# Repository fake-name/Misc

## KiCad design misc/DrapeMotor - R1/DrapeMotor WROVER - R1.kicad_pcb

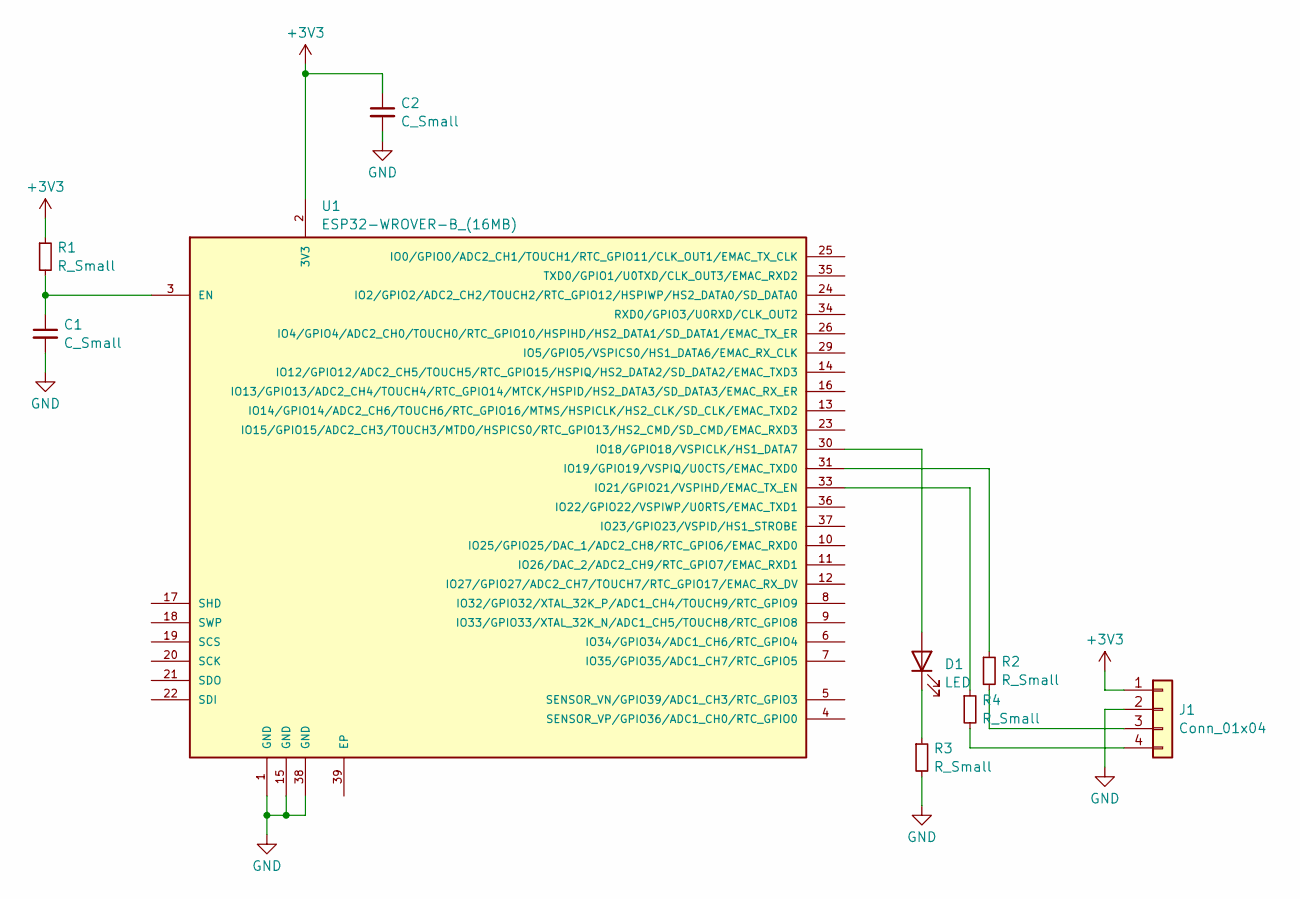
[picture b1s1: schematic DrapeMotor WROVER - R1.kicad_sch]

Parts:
C1, C2: C_Small; C_1206_3216Metric_Pad1.33x1.80mm_HandSolder
D1: LED; D_1206_3216Metric_Pad1.42x1.75mm_HandSolder
J1: Conn_01x04; PinSocket_1x04_P2.54mm_Vertical
R1, R2, R3, R4: R_Small; R_1206_3216Metric_Pad1.30x1.75mm_HandSolder
U1: ESP32-WROVER-B_(16MB); XCVR_ESP32-WROVER-B_(16MB); PARTREV 1.1

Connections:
+3V3: C2.1, J1.1, R1.1, U1.2 (3V3)
GND: C1.2, C2.2, J1.2, R3.2, U1.1 (GND), U1.15 (GND), U1.38 (GND)
unnamed: D1.2 (A), U1.30 (IO18/GPIO18/VSPICLK/HS1_DATA7)
unnamed: D1.1 (K), R3.1
unnamed: J1.3, R2.2
unnamed: J1.4, R4.2
unnamed: C1.1, R1.2, U1.3 (EN)
unnamed: R2.1, U1.31 (IO19/GPIO19/VSPIQ/U0CTS/EMAC_TXD0)
unnamed: R4.1, U1.33 (IO21/GPIO21/VSPIHD/EMAC_TX_EN)

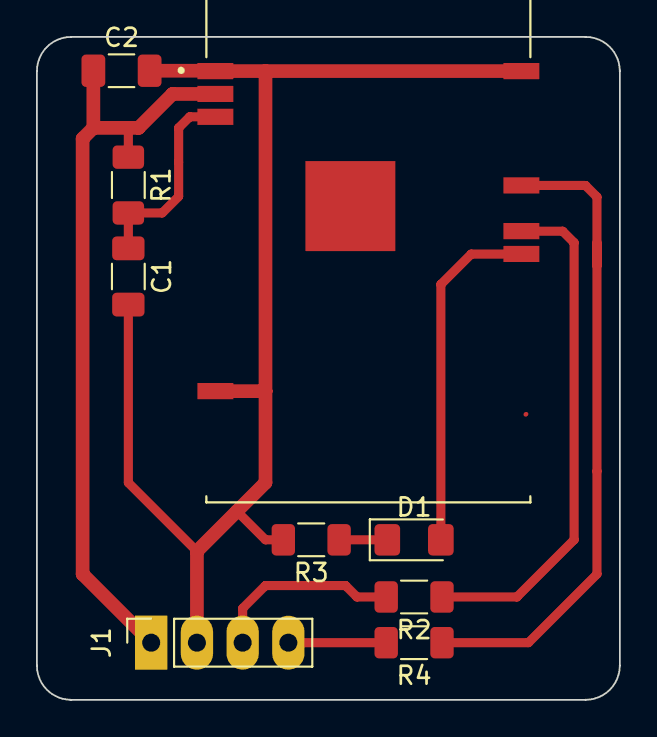
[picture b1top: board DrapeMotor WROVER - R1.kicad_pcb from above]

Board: 2 copper layers, 32.4 x 36.8 mm, 9 parts (0 on the bottom side), 9 nets.

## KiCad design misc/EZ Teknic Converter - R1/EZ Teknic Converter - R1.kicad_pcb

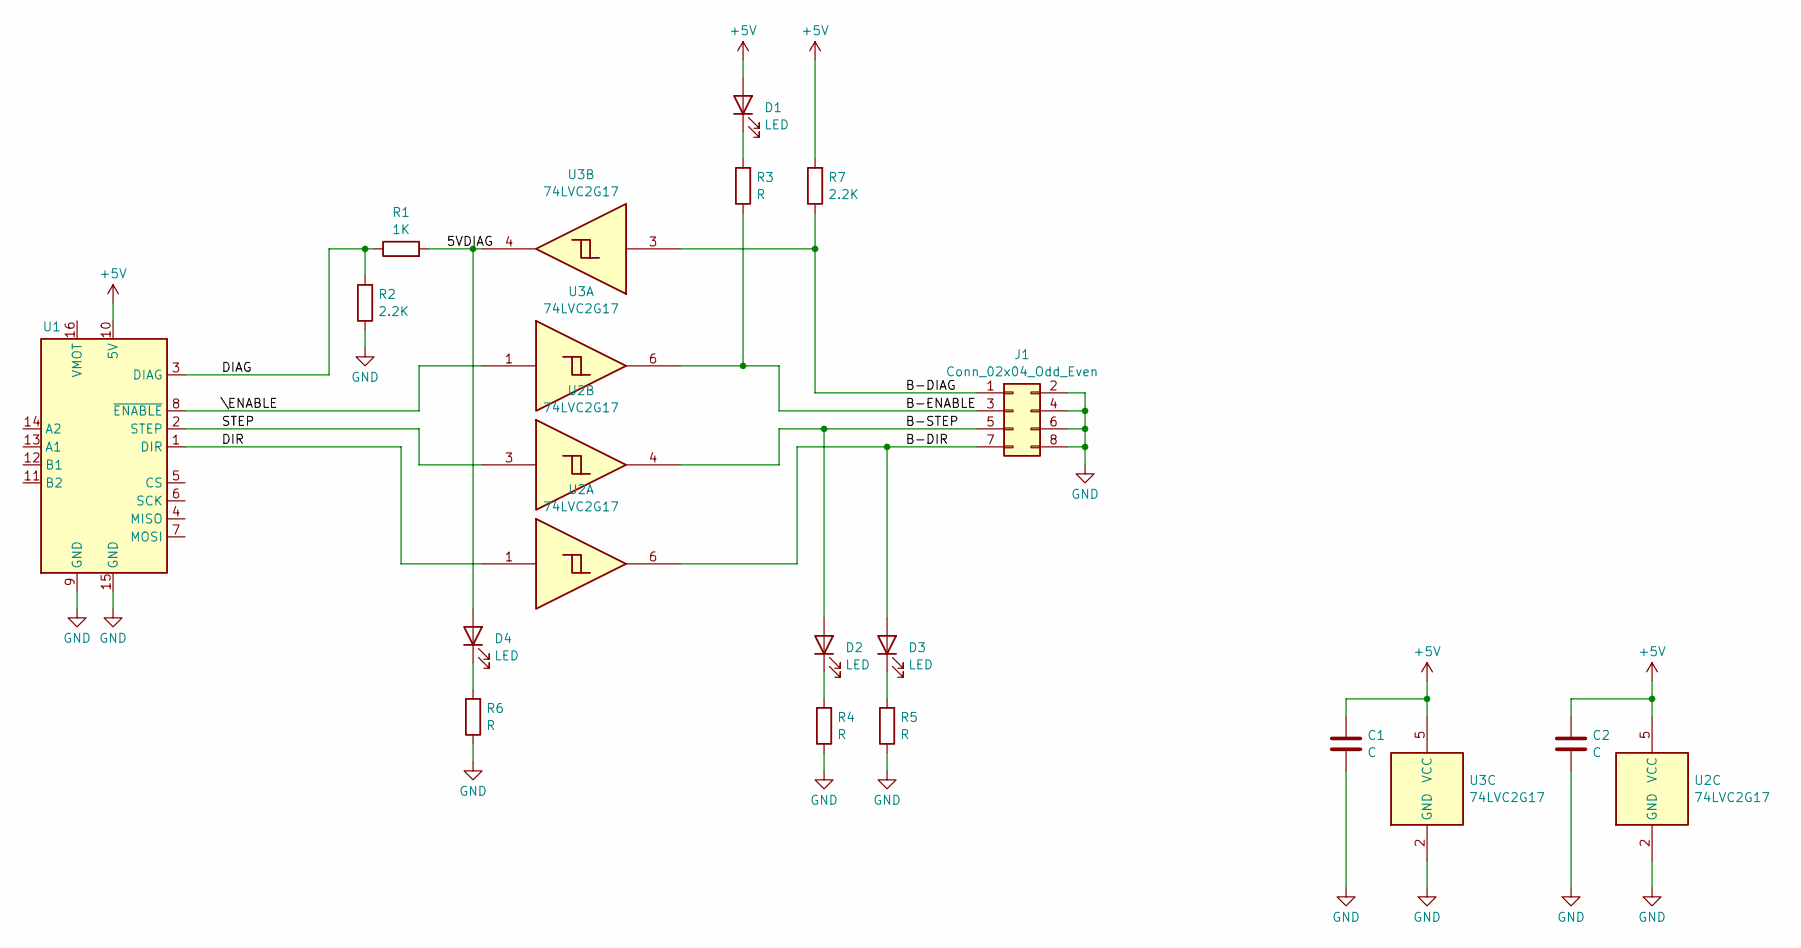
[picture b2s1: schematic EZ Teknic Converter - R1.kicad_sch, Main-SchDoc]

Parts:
C1, C2: C; C_0603_1608Metric
D1, D2, D3, D4: LED; LED_0603_1608Metric
J1: Conn_02x04_Odd_Even; Molex_PicoBlade_53261-0871_1x08-1MP_P1.25mm_Horizontal
R1: 1K; R_0603_1608Metric
R2, R7: 2.2K; R_0603_1608Metric
R3, R4, R5, R6: R; R_0603_1608Metric
U1: EZ Driver Interface; EZ_Stepper_Edge_Connector
U2, U3: 74LVC2G17; SOT-363_SC-70-6

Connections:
+5V: C1.1, C2.1, D1.2 (A), R7.2, U1.10 (5V), U2.5 (VCC), U3.5 (VCC)
/5VDIAG: D4.2 (A), R1.2, U3.4
/B-DIAG: J1.1, R7.1, U3.3
/B-DIR: D3.2 (A), J1.7, U2.6
/B-ENABLE: J1.3, R3.1, U3.6
/B-STEP: D2.2 (A), J1.5, U2.4
/DIAG: R1.1, R2.2, U1.3 (DIAG)
/DIR: U1.1 (DIR), U2.1
/STEP: U1.2 (STEP), U2.3
/\ENABLE: U1.8 (~ENABLE), U3.1
GND: C1.2, C2.2, J1.2, J1.4, J1.6, J1.8, J1.MP, R2.1, R4.1, R5.1, R6.1, U1.9 (GND), U1.15 (GND), U2.2 (GND), U3.2 (GND)
unnamed: D1.1 (K), R3.2
unnamed: D2.1 (K), R4.2
unnamed: D3.1 (K), R5.2
unnamed: D4.1 (K), R6.2

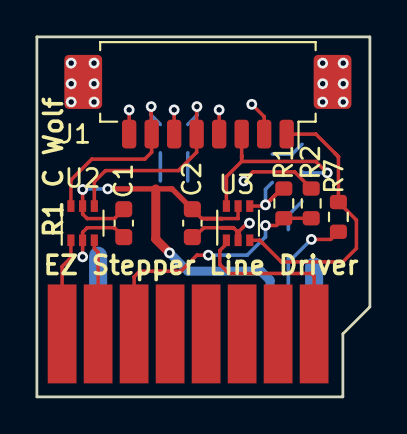
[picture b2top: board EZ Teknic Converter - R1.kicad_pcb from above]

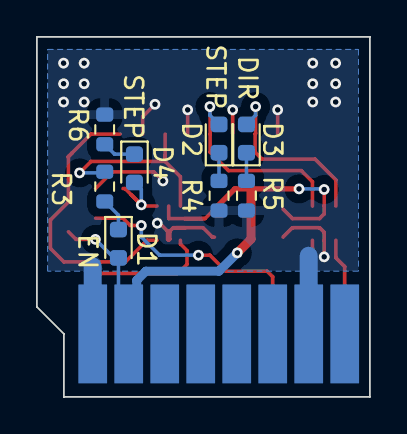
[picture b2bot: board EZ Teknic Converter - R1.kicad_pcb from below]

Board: 2 copper layers, 18.5 x 20.0 mm, 17 parts (8 on the bottom side), 15 nets.

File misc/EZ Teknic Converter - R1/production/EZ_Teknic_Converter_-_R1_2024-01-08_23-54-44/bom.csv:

Designator,Footprint,Quantity,Value,LCSC Part #
"C1, C2",0603,2,C,
"D1, D2, D3, D4",0603,4,LED,
J1,Molex_PicoBlade_53261-0871_1x08-1MP_P1.25mm_Horizontal,1,Conn_02x04_Odd_Even,
R1,0603,1,1K,
"R2, R7",0603,2,2.2K,
"R3, R4, R5, R6",0603,4,R,
U1,EZ_Stepper_Edge_Connector,1,EZ Driver Interface,
"U2, U3",SOT-363_SC-70-6,2,74LVC2G17,

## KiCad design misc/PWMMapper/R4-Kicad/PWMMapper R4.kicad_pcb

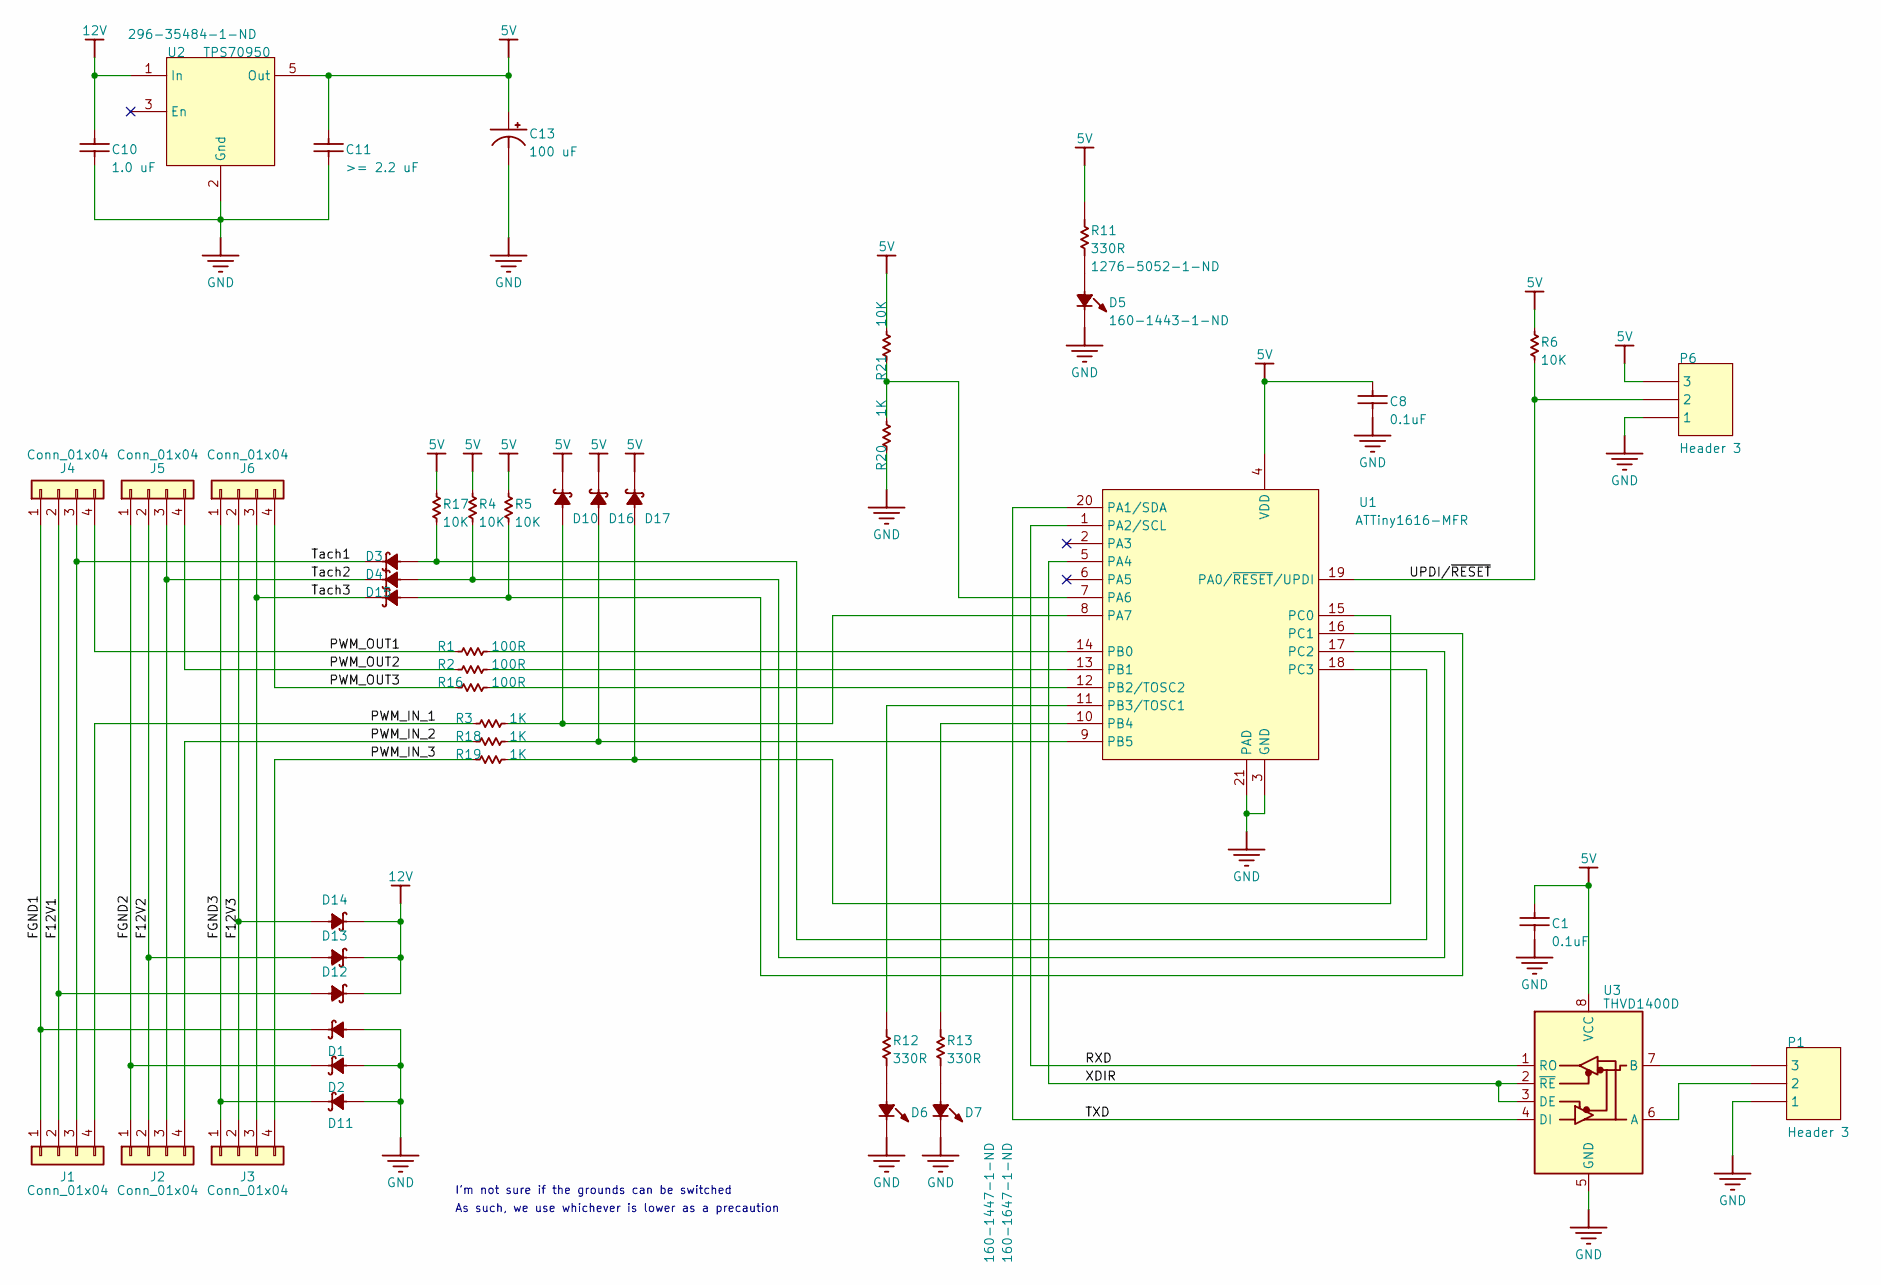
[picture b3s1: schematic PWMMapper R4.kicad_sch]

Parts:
C1, C8: Cap; C_0603_1608Metric
C10, C11: Cap; C_1206_3216Metric
C13: 100 uF; CP_EIA-3528-21_Kemet-B
D1, D2, D3, D4, D10, D11, D12, D13, D14, D15, D16, D17: Schottky Diode; D_SOD-323
D5, D6, D7: LED0; D_0603_1608Metric
J1, J2, J3, J4, J5, J6: Conn_01x04; TerminalBlock_TE_282834-4_1x04_P2.54mm_Horizontal
P1: Header 3; JST_XH_B3B-XH-AM_1x03_P2.50mm_Vertical
P6: Header 3; PinHeader_1x03_P2.54mm_Vertical
R1, R2, R3, R4, R5, R6, R16, R17, R18, R19, R20, R21: Res Semi Small; R_0603_1608Metric
R11, R12, R13: Res Semi; R_0603_1608Metric
U1: ATTiny1616-MFR; QFN-20-1EP_3x3mm_P0.4mm_EP1.65x1.65mm
U2: TPS70950; SOT-23-5
U3: THVD1400D; SOIC-8_3.9x4.9mm_P1.27mm

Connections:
5V: C1.2, C8.2, C11.2, C13.1, D10.1, D16.1, D17.1, P6.3, R4.2, R5.2, R6.2, R11.2, R17.2, R21.2, U1.4 (VDD), U2.5 (Out), U3.8 (VCC)
12V: C10.2, D12.1, D13.1, D14.1, U2.1 (In)
/F12V1: D12.2, J1.2, J4.2
/F12V2: D13.2, J2.2, J5.2
/F12V3: D14.2, J3.2, J6.2
/FGND1: D1.1, J1.1, J4.1
/FGND2: D2.1, J2.1, J5.1
/FGND3: D11.1, J3.1, J6.1
/PWM_IN_1: J1.4, R3.1
/PWM_IN_2: J2.4, R18.1
/PWM_IN_3: J3.4, R19.1
/PWM_OUT1: J4.4, R1.1
/PWM_OUT2: J5.4, R2.1
/PWM_OUT3: J6.4, R16.1
/RXD: U1.1 (PA2/SCL), U3.1 (RO)
/TXD: U1.20 (PA1/SDA), U3.4 (DI)
/Tach1: D3.1, J1.3, J4.3
/Tach2: D4.1, J2.3, J5.3
/Tach3: D15.1, J3.3, J6.3
/UPDI/~RESET: P6.2, R6.1, U1.19 (PA0/~RESET/UPDI)
/XDIR: U1.5 (PA4), U3.2 (~RE), U3.3 (DE)
GND: C1.1, C8.1, C10.1, C11.1, C13.2, D1.2, D2.2, D5.2, D6.2, D7.2, D11.2, P1.1, P6.1, R20.1, U1.3 (GND), U1.21 (PAD), U2.2 (Gnd), U3.5 (GND)
unnamed: D5.1, R11.1
unnamed: D6.1, R12.1
unnamed: D7.1, R13.1
unnamed: R20.2, R21.1, U1.7 (PA6)
unnamed: D10.2, R3.2, U1.8 (PA7)
unnamed: R1.2, U1.14 (PB0)
unnamed: R2.2, U1.13 (PB1)
unnamed: R16.2, U1.12 (PB2/TOSC2)
unnamed: R12.2, U1.11 (PB3/TOSC1)
unnamed: R13.2, U1.10 (PB4)
unnamed: D16.2, R18.2, U1.9 (PB5)
unnamed: D17.2, R19.2, U1.15 (PC0)
unnamed: D15.2, R5.1, U1.16 (PC1)
unnamed: D4.2, R4.1, U1.17 (PC2)
unnamed: D3.2, R17.1, U1.18 (PC3)
unnamed: P1.2, U3.6 (A)
unnamed: P1.3, U3.7 (B)

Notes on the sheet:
As such, we use whichever is lower as a precaution
I'm not sure if the grounds can be switched

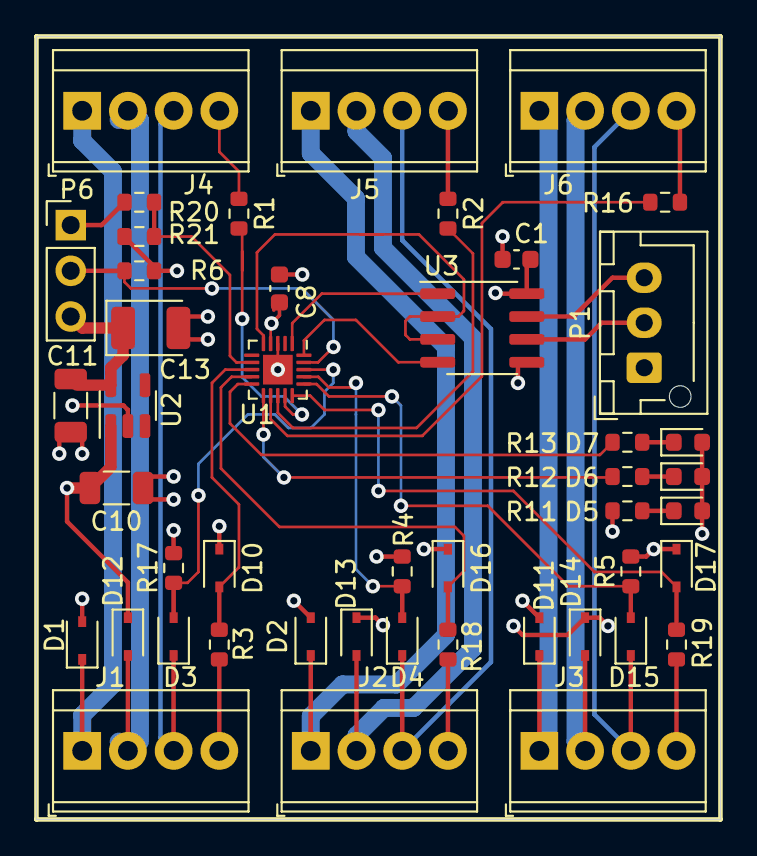
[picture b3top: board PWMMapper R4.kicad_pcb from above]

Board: 4 copper layers, 38.0 x 43.5 mm, 46 parts (0 on the bottom side), 39 nets.

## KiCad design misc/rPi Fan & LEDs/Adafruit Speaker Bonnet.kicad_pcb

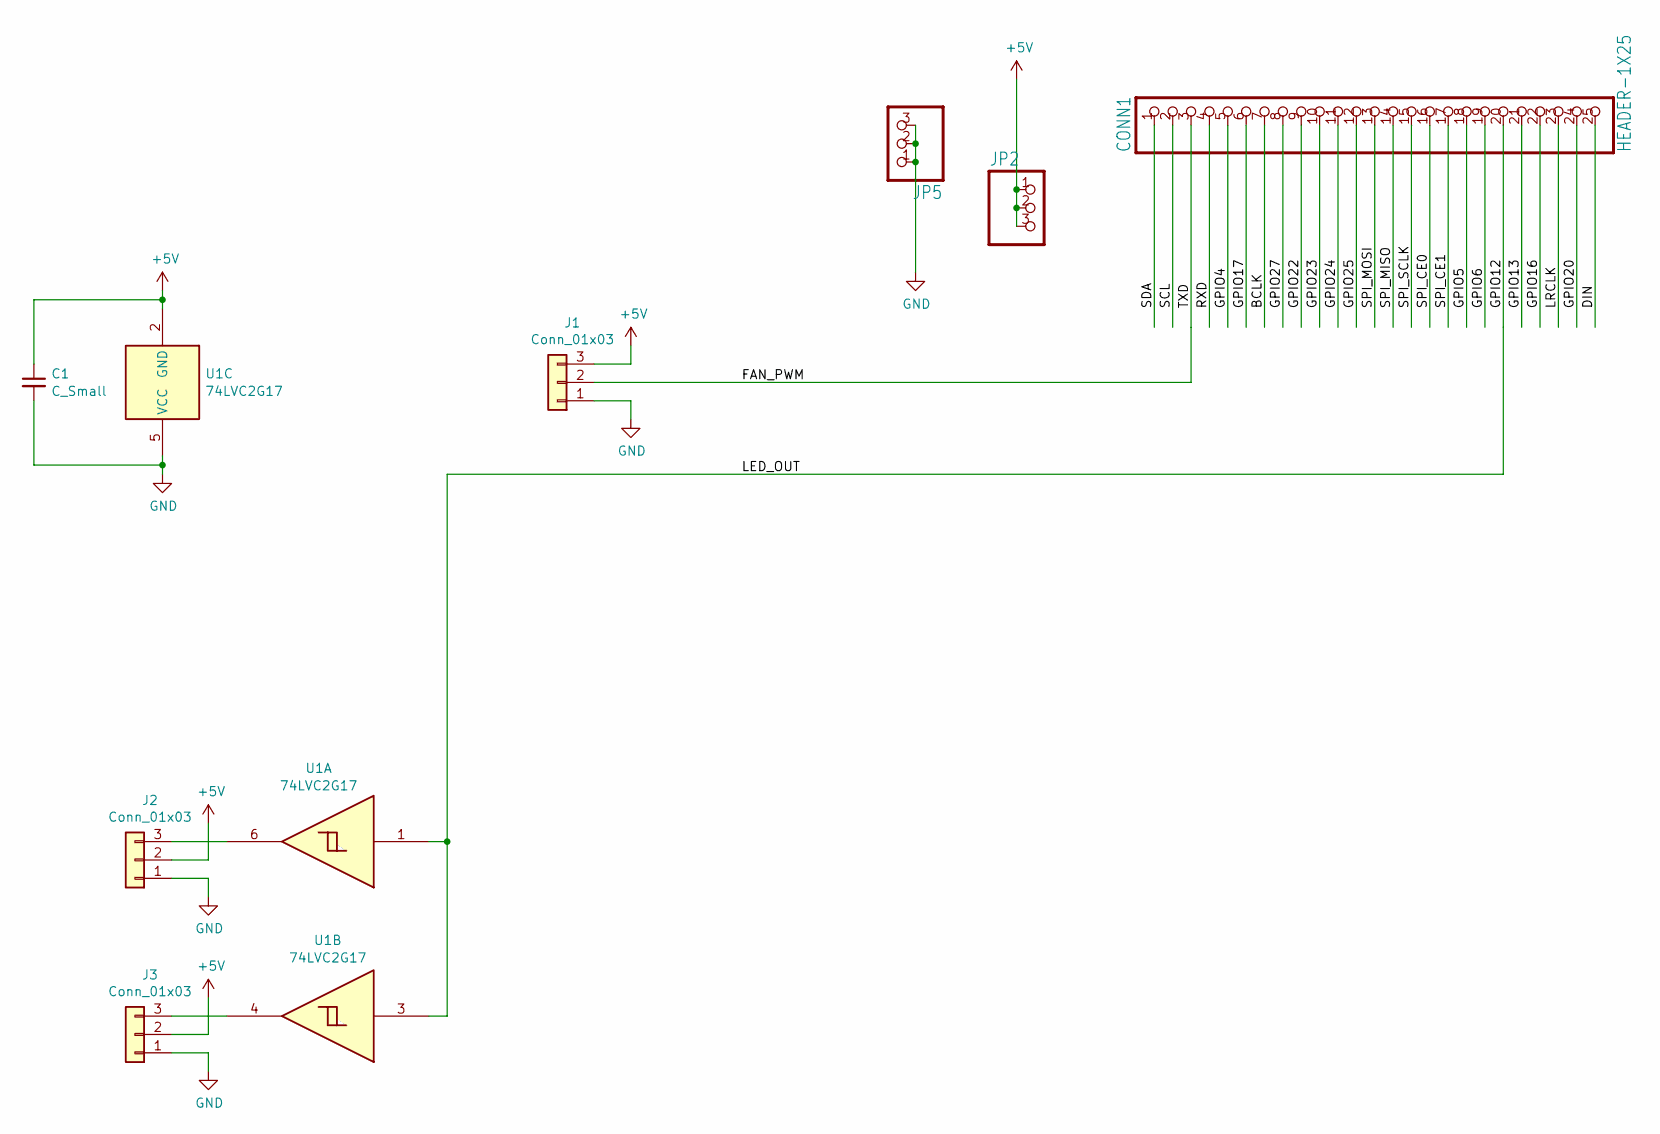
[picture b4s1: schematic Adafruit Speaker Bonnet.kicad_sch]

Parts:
C1: C_Small; C_0603_1608Metric
CONN1: HEADER-1X25; 1X25_ROUND_70MIL
J1, J2, J3: Conn_01x03; JST_GH_SM03B-GHS-TB_1x03-1MP_P1.25mm_Horizontal
JP2, JP5: HEADER-1X376MIL; 1X03_ROUND_76
U1: 74LVC2G17; SOT-23-6

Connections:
+5V: C1.1, J1.3, J2.2, J3.2, JP2.1, JP2.2, JP2.3, U1.2 (GND)
/BCLK: CONN1.7
/DIN: CONN1.25
/FAN_PWM: CONN1.3, J1.2
/GPIO4: CONN1.5
/GPIO5: CONN1.18
/GPIO6: CONN1.19
/GPIO12: CONN1.20, U1.1, U1.3
/GPIO13: CONN1.21
/GPIO16: CONN1.22
/GPIO17: CONN1.6
/GPIO20: CONN1.24
/GPIO22: CONN1.9
/GPIO23: CONN1.10
/GPIO24: CONN1.11
/GPIO25: CONN1.12
/GPIO27: CONN1.8
/LRCLK: CONN1.23
/RXD: CONN1.4
/SCL: CONN1.2
/SDA: CONN1.1
/SPI_CE0: CONN1.16
/SPI_CE1: CONN1.17
/SPI_MISO: CONN1.14
/SPI_MOSI: CONN1.13
/SPI_SCLK: CONN1.15
GND: C1.2, J1.1, J2.1, J3.1, JP5.1, JP5.2, JP5.3, U1.5 (VCC)
unnamed: J2.3, U1.6
unnamed: J3.3, U1.4

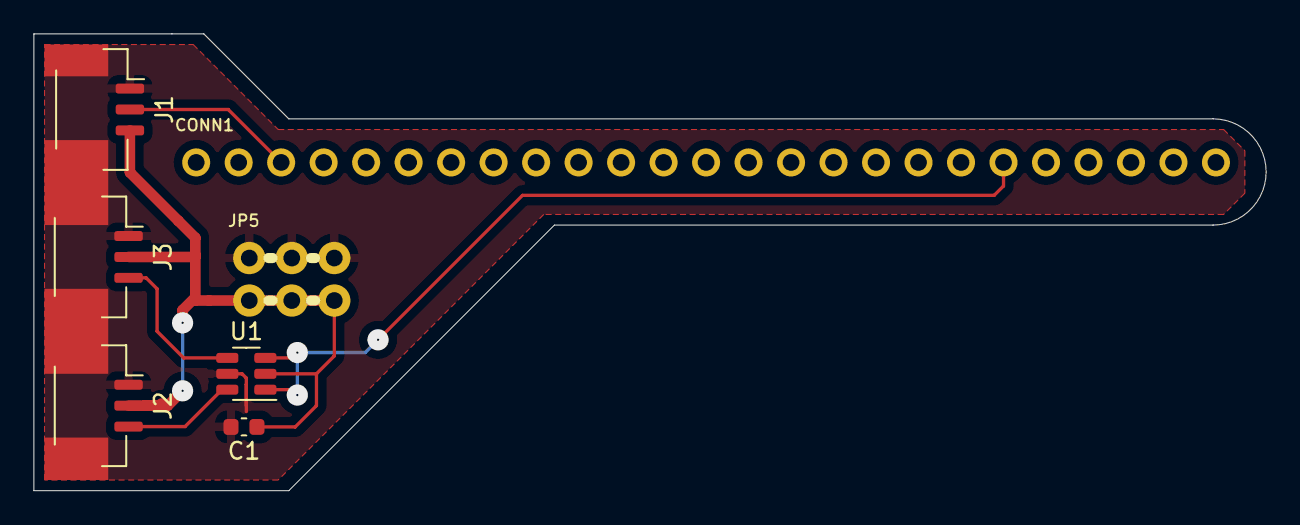
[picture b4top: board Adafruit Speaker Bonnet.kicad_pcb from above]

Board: 2 copper layers, 73.7 x 27.3 mm, 8 parts (0 on the bottom side), 6 nets.

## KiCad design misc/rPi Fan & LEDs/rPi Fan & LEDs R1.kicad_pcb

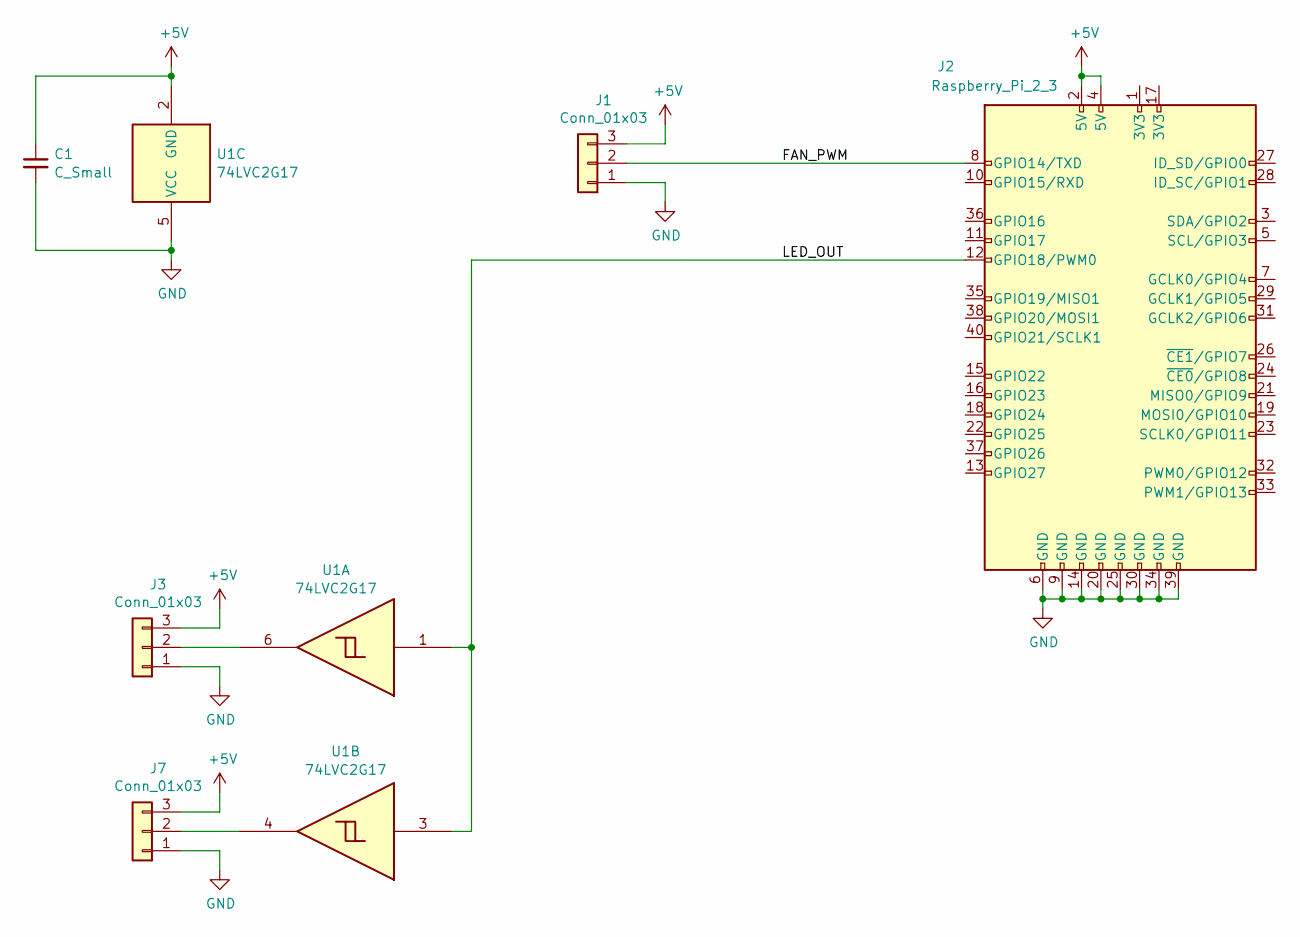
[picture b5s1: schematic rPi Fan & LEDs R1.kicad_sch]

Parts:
C1: C_Small; C_0603_1608Metric
J1, J3, J7: Conn_01x03; JST_XH_B3B-XH-AM_1x03_P2.50mm_Vertical
J2: Raspberry_Pi_2_3; PinHeader_2x20_P2.54mm_Vertical
U1: 74LVC2G17; SOT-23-6

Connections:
+5V: C1.1, J1.3, J2.2 (5V), J2.4 (5V), J3.3, J7.3, U1.2 (GND)
/FAN_PWM: J1.2, J2.8 (GPIO14/TXD)
/LED_OUT: J2.12 (GPIO18/PWM0), U1.1, U1.3
GND: C1.2, J1.1, J2.6 (GND), J2.9 (GND), J2.14 (GND), J2.20 (GND), J2.25 (GND), J2.30 (GND), J2.34 (GND), J2.39 (GND), J3.1, J7.1, U1.5 (VCC)
unnamed: J3.2, U1.6
unnamed: J7.2, U1.4

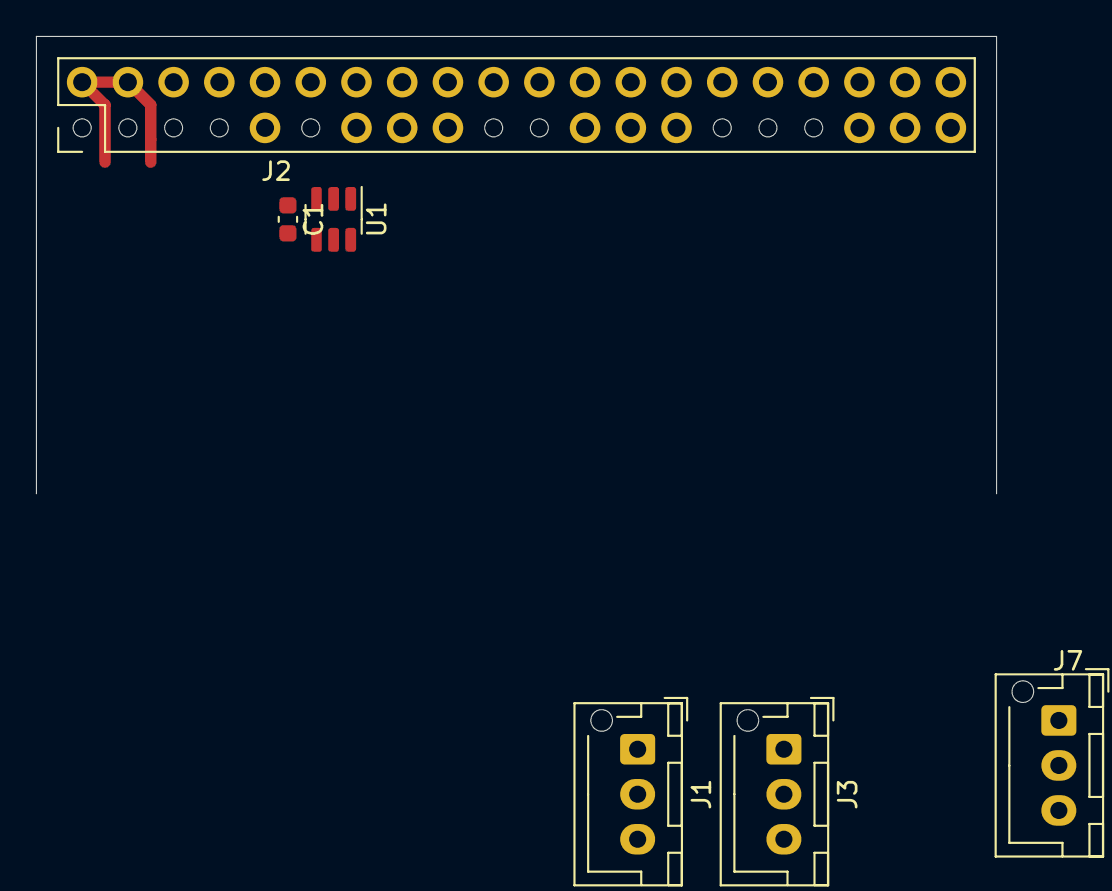
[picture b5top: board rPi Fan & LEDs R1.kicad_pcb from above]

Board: 2 copper layers, 6 parts (0 on the bottom side), 6 nets.
